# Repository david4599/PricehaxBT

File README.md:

# Pricehax BT
Wireless prototype based on Arduino Nano + HC-06 (or HC-05) Bluetooth module implementing [Furrtek's ESL reverse engineering project](http://furrtek.free.fr/index.php?a=esl).

This tool receives ESL data from the included PricehaxBT Android app. It is a decompiled (see [Notes](https://github.com/david4599/PricehaxBT#notes)) and updated version of Pricehax, an old app originally made by Furrtek which was using audio to transmit data to a homemade dongle.

For archival sake, Furrtek's videos of the whole research process are backed up in this [playlist](https://www.youtube.com/playlist?list=PLhEz48id1qqD27sRc73mDFfBpu_RcLxfZ) (most in French, auto-translated subtitles are available but they are far from perfect).

**For educational purposes and fun only.** Both Furrtek and I decline all responsability for any kind of issues related to an illegal use of this repo. Be smart, the prices in the store's database won't change, you have been warned.

_Update:_ Furrtek recently reworked and updated the app to communicate with his ESL Blaster dongle. Check out his version on the [PrecIR repo](https://github.com/furrtek/PrecIR).

## Build
- Create the dongle on breadboard by following the schematic (or order the pcb and solder the components)
- Configure the HC-05/HC-06 module using the AT commands to change its name to "PRICEHAX TX V3" (without the quotes) and its baudrate to 115200bps
- Program the Arduino Nano with the included sketch
- Download and install the [Android app](https://github.com/david4599/PricehaxBT/releases/latest)
- Pair the dongle in the phone settings and go to the app. The HC-05/HC-06 module should connect automatically, its LED should stay on and not blink anymore (scroll the tabs list and go to the config tab for manual connection/disconnection)
- Enjoy ;-)

## Android app changelog

### Version 1.4 (22)

**Features**

- Added a few ESL types

### Version 1.3 (21)

**Features**
- Added PP16 IR Protocol support (not full speed, see [Notes](https://github.com/david4599/PricehaxBT#notes)): [speed comparison video](https://youtu.be/DFfLOQh_ERs)
- Updated camera autofocus handling by using continuous focus modes if available
- Improved Bluetooth transmission reliability: the whole data (Pricehax header + PPM frame) is sent to the dongle with a basic checksum instead of using the PPM frame CRC that won't verify the header

**Fixes**
- Fixed bug that was sometimes stopping the image transmission just after the wake-up frame
- Fixed camera preview rotation in reverse landscape and reverse portrait orientations
- Fixed waiting time when sending an image in 2 parts (due to 64kB limit)

### Version 1.2 (20)

**Features**
- Added 1370 and 1371 ESL types (ST HD L Red and ST HD150 Red black housing versions)
- Added checksum verification of the ESL barcode

**Fixes**
- Fixed SmartTag HD T definition in information label

### Version 1.2 (19)

**Features**
- Added a mode to enter the barcode manually

### Version 1.1 (18)

**Features**
- Red (yellow not tested) ESLs are supported: https://youtu.be/0PFMIiDluDw
- Improved Bluetooth transmission reliability: comparison of received checksum and calculated checksum by the dongle
- Added the possibility to stop sending the current image

**Fixes**
- Fixed ST HD150 and ST HD200 definitions

### Version 1.1 (17)

**Features**
- Added the ability to scroll if pages are greater than the height of the screen (especially in landscape mode)
- Display debug infos for 24h
- Hide debug infos feature added
- Ability to blink the green LED on ST ESLs (not working yet on some): https://youtu.be/b0Rn40alxQg
- Start autofocus by touching the preview screen on "PLID Scan" tab (not working sometimes?)
- ESL types added (mainly graphic ESLs, not tested on the most of them but it should work)
- Automatically choose sending compressed or raw data to graphic ESLs
- Ability to force sending uncompressed data to graphic ESLs
- The number of frames repeats for graphic ESLs can be chosen (speed transmission vs reliability)
- The dongle can be manually connected or disconnected in "Config" tab

**Fixes**
- Fixed some bugs and app crashes

## Notes
- The implemented PP4C and PP16 protocols are not transmitting data at their maximum speeds. In theory, they should be around 10kbps for PP4C and 38kbps for PP16. Pricehax BT seems to do only 6kbps and 11kbps if my calculations are correct
- I didn't write the app, I simply decompiled the original Pricehax apk with an online apk decompiler website. Then, I imported the sources on Android Studio and fixed the decompilation errors preventing the re-compilation
- The app supports Bluetooth only, the communication using audio has been disabled (not the goal of this repo)
- Furrtek did code the Bluetooth feature in the original app, I just made some changes so the feature works with my dongle
- I am not a programming or electronic expert, so the code and the schematic might be better...

#

Copyright (c) Furrtek 2014 & david4599 2019 - 2024

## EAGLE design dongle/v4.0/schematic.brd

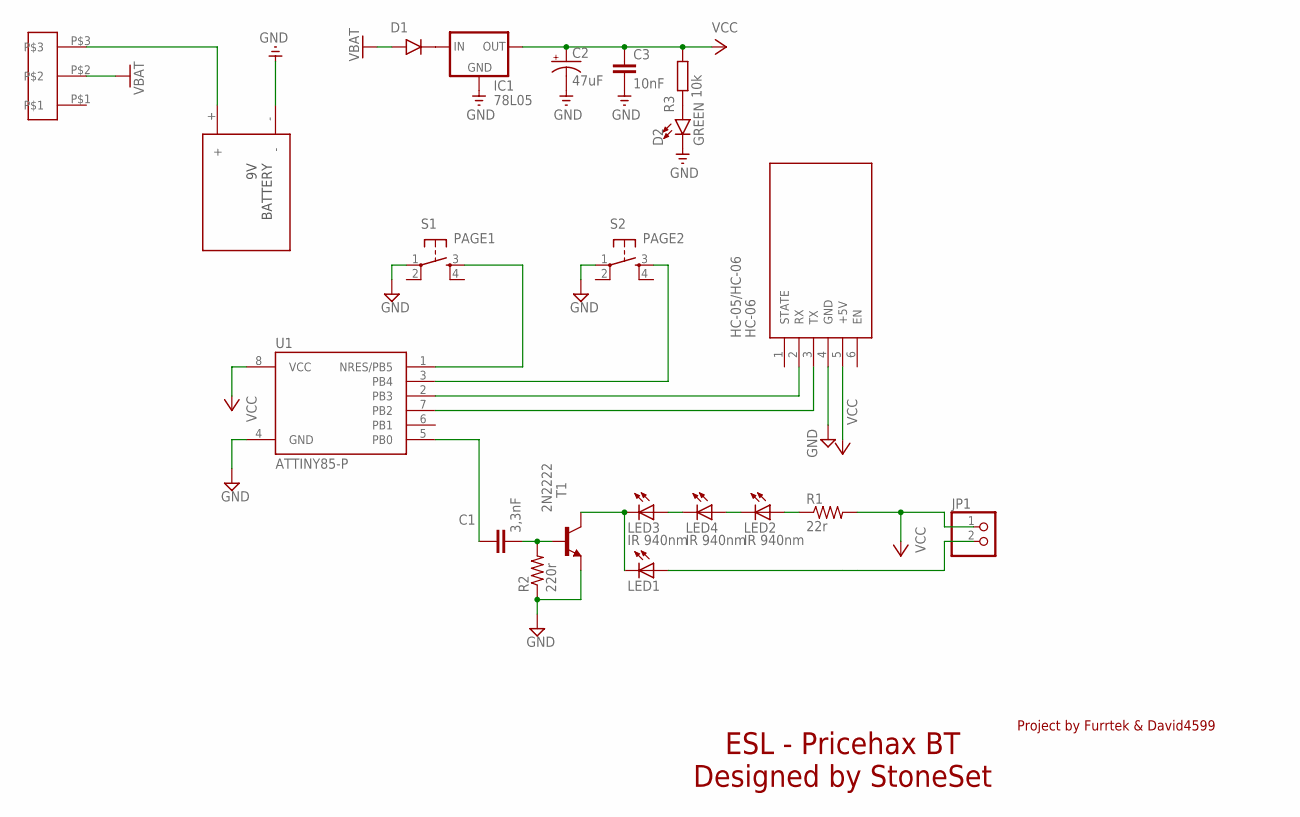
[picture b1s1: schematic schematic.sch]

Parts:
C1: 3,3nF; C2.5-3
C2: 47uF; CPOL-RADIAL-10UF-25V
C3: 10nF; CAP-PTH-10MM
D1: 1N4001; DO41-10
D2: GREEN; LED_3MM-NS
HC-05/HC-06: HC-06; WIRELESS-BLUETOOTH-HC-05
IC1: 78L05; 78XXL
JP1: PINHD-1X2; 1X02
LED1: LED5MM
LED2, LED3, LED4: IR 940nm; LED5MM
R1: 22r; 0204/7
R2: 220r; 0204/7
R3: 10k; 0207/7
S1: PAGE1; DTS-6
S2: PAGE2; DTS-6
T1: 2N2222; TO92-EBC-OVAL
U1: ATTINY85-P; PDIP08_300MIL
U$2: PACKAGESWITCH; SLIDESWITCH
U$3: BAT

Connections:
GND: C2.2 (-), C3.2, D2.K (C), HC-05/HC-06.4 (GND), IC1.GND, R2.1, S1.1, S2.1, T1.E, U1.4 (GND), U$3.-
unnamed: LED1.K (C), LED3.K (C), T1.C
unnamed: C1.2, R2.2, T1.B
unnamed: C1.1, U1.5 (PB0)
unnamed: LED3.A, LED4.K (C)
unnamed: LED2.K (C), LED4.A
unnamed: LED2.A, R1.1
unnamed: JP1.2, LED1.A
unnamed: S1.3, U1.1 (NRES/PB5)
unnamed: HC-05/HC-06.2 (RX), U1.2 (PB3)
unnamed: S2.3, U1.3 (PB4)
unnamed: HC-05/HC-06.3 (TX), U1.7 (PB2)
unnamed: D1.C (CATHODE), IC1.IN
unnamed: U$2.P$3, U$3.+
unnamed: D2.A, R3.1
VBAT: D1.A (ANODE), U$2.P$2
VCC: C2.1 (+), C3.1, HC-05/HC-06.5 (+5V), IC1.OUT, JP1.1, R1.2, R3.2, U1.8 (VCC)

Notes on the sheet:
ESL - Pricehax BT Designed by StoneSet
Project by Furrtek & David4599

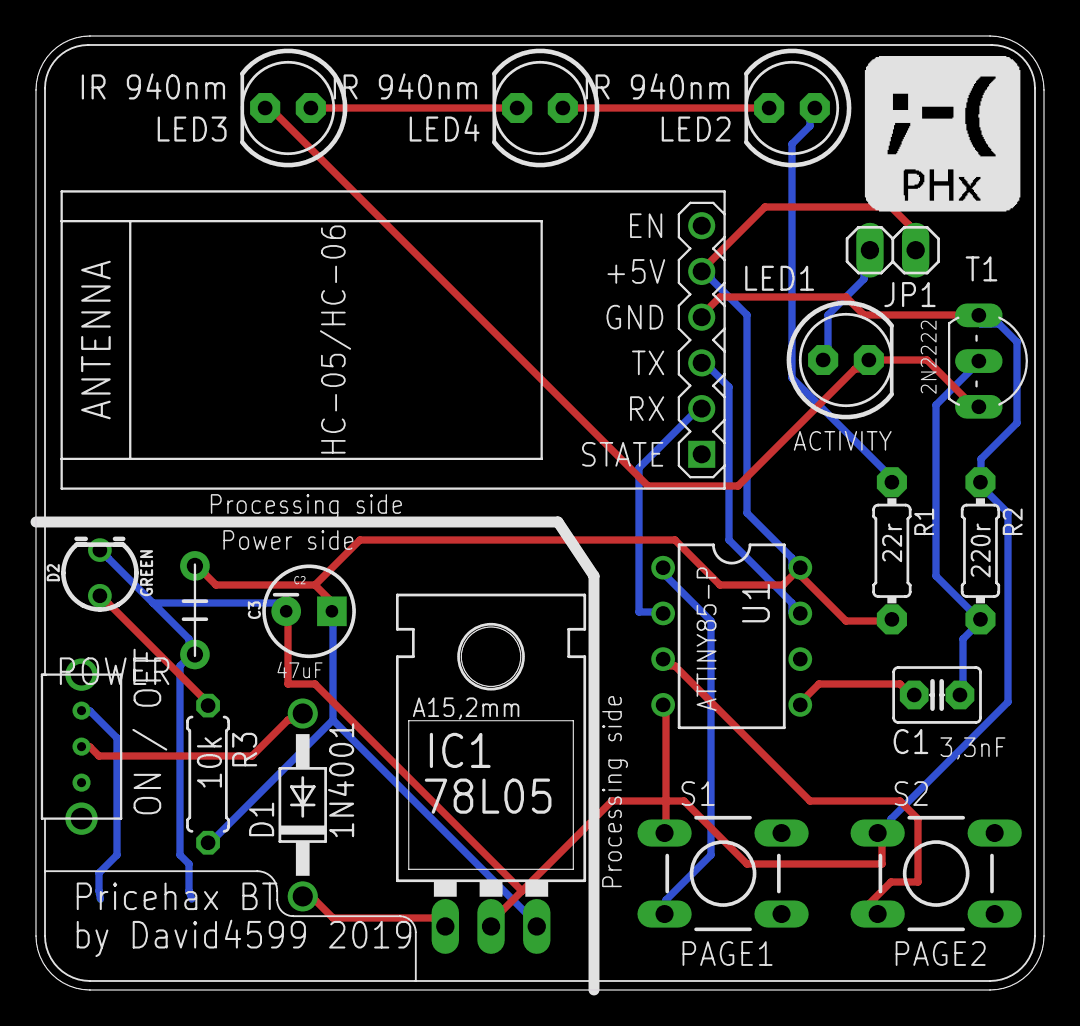
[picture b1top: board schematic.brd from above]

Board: 2 copper layers, 56.0 x 53.0 mm, 21 parts (1 on the bottom side), 17 nets.

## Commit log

2019-08-11 project added
2019-08-11 fix readme
2019-08-11 fix prog
2019-08-11 add pcb img
2019-08-13 add note in readme
2019-08-15 [WIP] feat(pcb): new version of the PCB {see description}
    - use attiny85 instead of Arduino nano
    - add two buttons to change pages without a phone
    - add 9V regulator (7805)
2019-09-10 dongle program optimized, moved dongle files, update readme
2019-09-12 fixed crash and bug
2019-09-14 updated apk
2019-09-17 added link to videos
2019-09-18 replaced image
2019-10-02 Pricehax BT V18.0 released
2020-03-21 Added PLID in LED flashing command
2020-03-24 Removed logo
2021-06-19 Added manual barcode setting, updated readme and versioning
2022-08-18 Update MainActivity.java
    New hardware type ID 1370, 2021 model - SmartTag HD L 296x128 in a black housing
2022-08-19 Added 1371 ESL type and removed experimental string from ST HD L Red type
2022-08-19 Fixed bad resolution in ST HD T Red type string
2022-08-19 Added checksum verification of the barcode
2022-08-19 Fixed MainActivity.java
2022-08-20 Put the ino file in a folder with the proper name otherwise the Arduino IDE will complain and automatically create the folder which will affect the git local repo
2022-08-20 Changed version in comment
2022-08-27 Fixed version bump
2022-08-27 Added Version 1.2 (20) in changelog
2022-09-09 Pricehax BT V1.3 (21) Released
    Added PP16 IR protocol support (not full speed)
    Updated camera autofocus handling
    Improved Bluetooth transmission reliability: basic checksum of the whole data (including Pricehax header) instead of using the PPM frame CRC
    Adjusted page changing repeat timings for PP16
    Fixed bug that was sometimes stopping the image transmission just after the wake-up frame
    Fixed camera preview rotation
2022-09-09 Updated arduino dongle code to support PP16 IR protocol + refactoring
2023-04-20 Add files via upload
    Add support for 1628
2023-04-20 Add support for 1628
2023-04-27 Add support for 1243 Continuum HCN
2023-04-27 Add support for 1243 Continuum HCN
    Add support for 1243 Continuum HCN
2023-04-28 Support for 1627
2023-04-30 Update MainActivity
    fixes
2023-04-30 fix #2
2023-04-30 Fixed 1242 model
2023-04-30 Removed EXPERIMENTAL text from 1315 model
2024-02-25 Updated readme + version bump

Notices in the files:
parts and their libraries:
diy-modules: Released under the Creative Commons Attribution 4.0 International License: http://creativecommons.org/licenses/by/4.0
SparkFun-Capacitors: Licensing: Creative Commons ShareAlike 4.0 International - https://creativecommons.org/licenses/by-sa/4.0
supply0: Copyright (C) 2007, Bob Starr
